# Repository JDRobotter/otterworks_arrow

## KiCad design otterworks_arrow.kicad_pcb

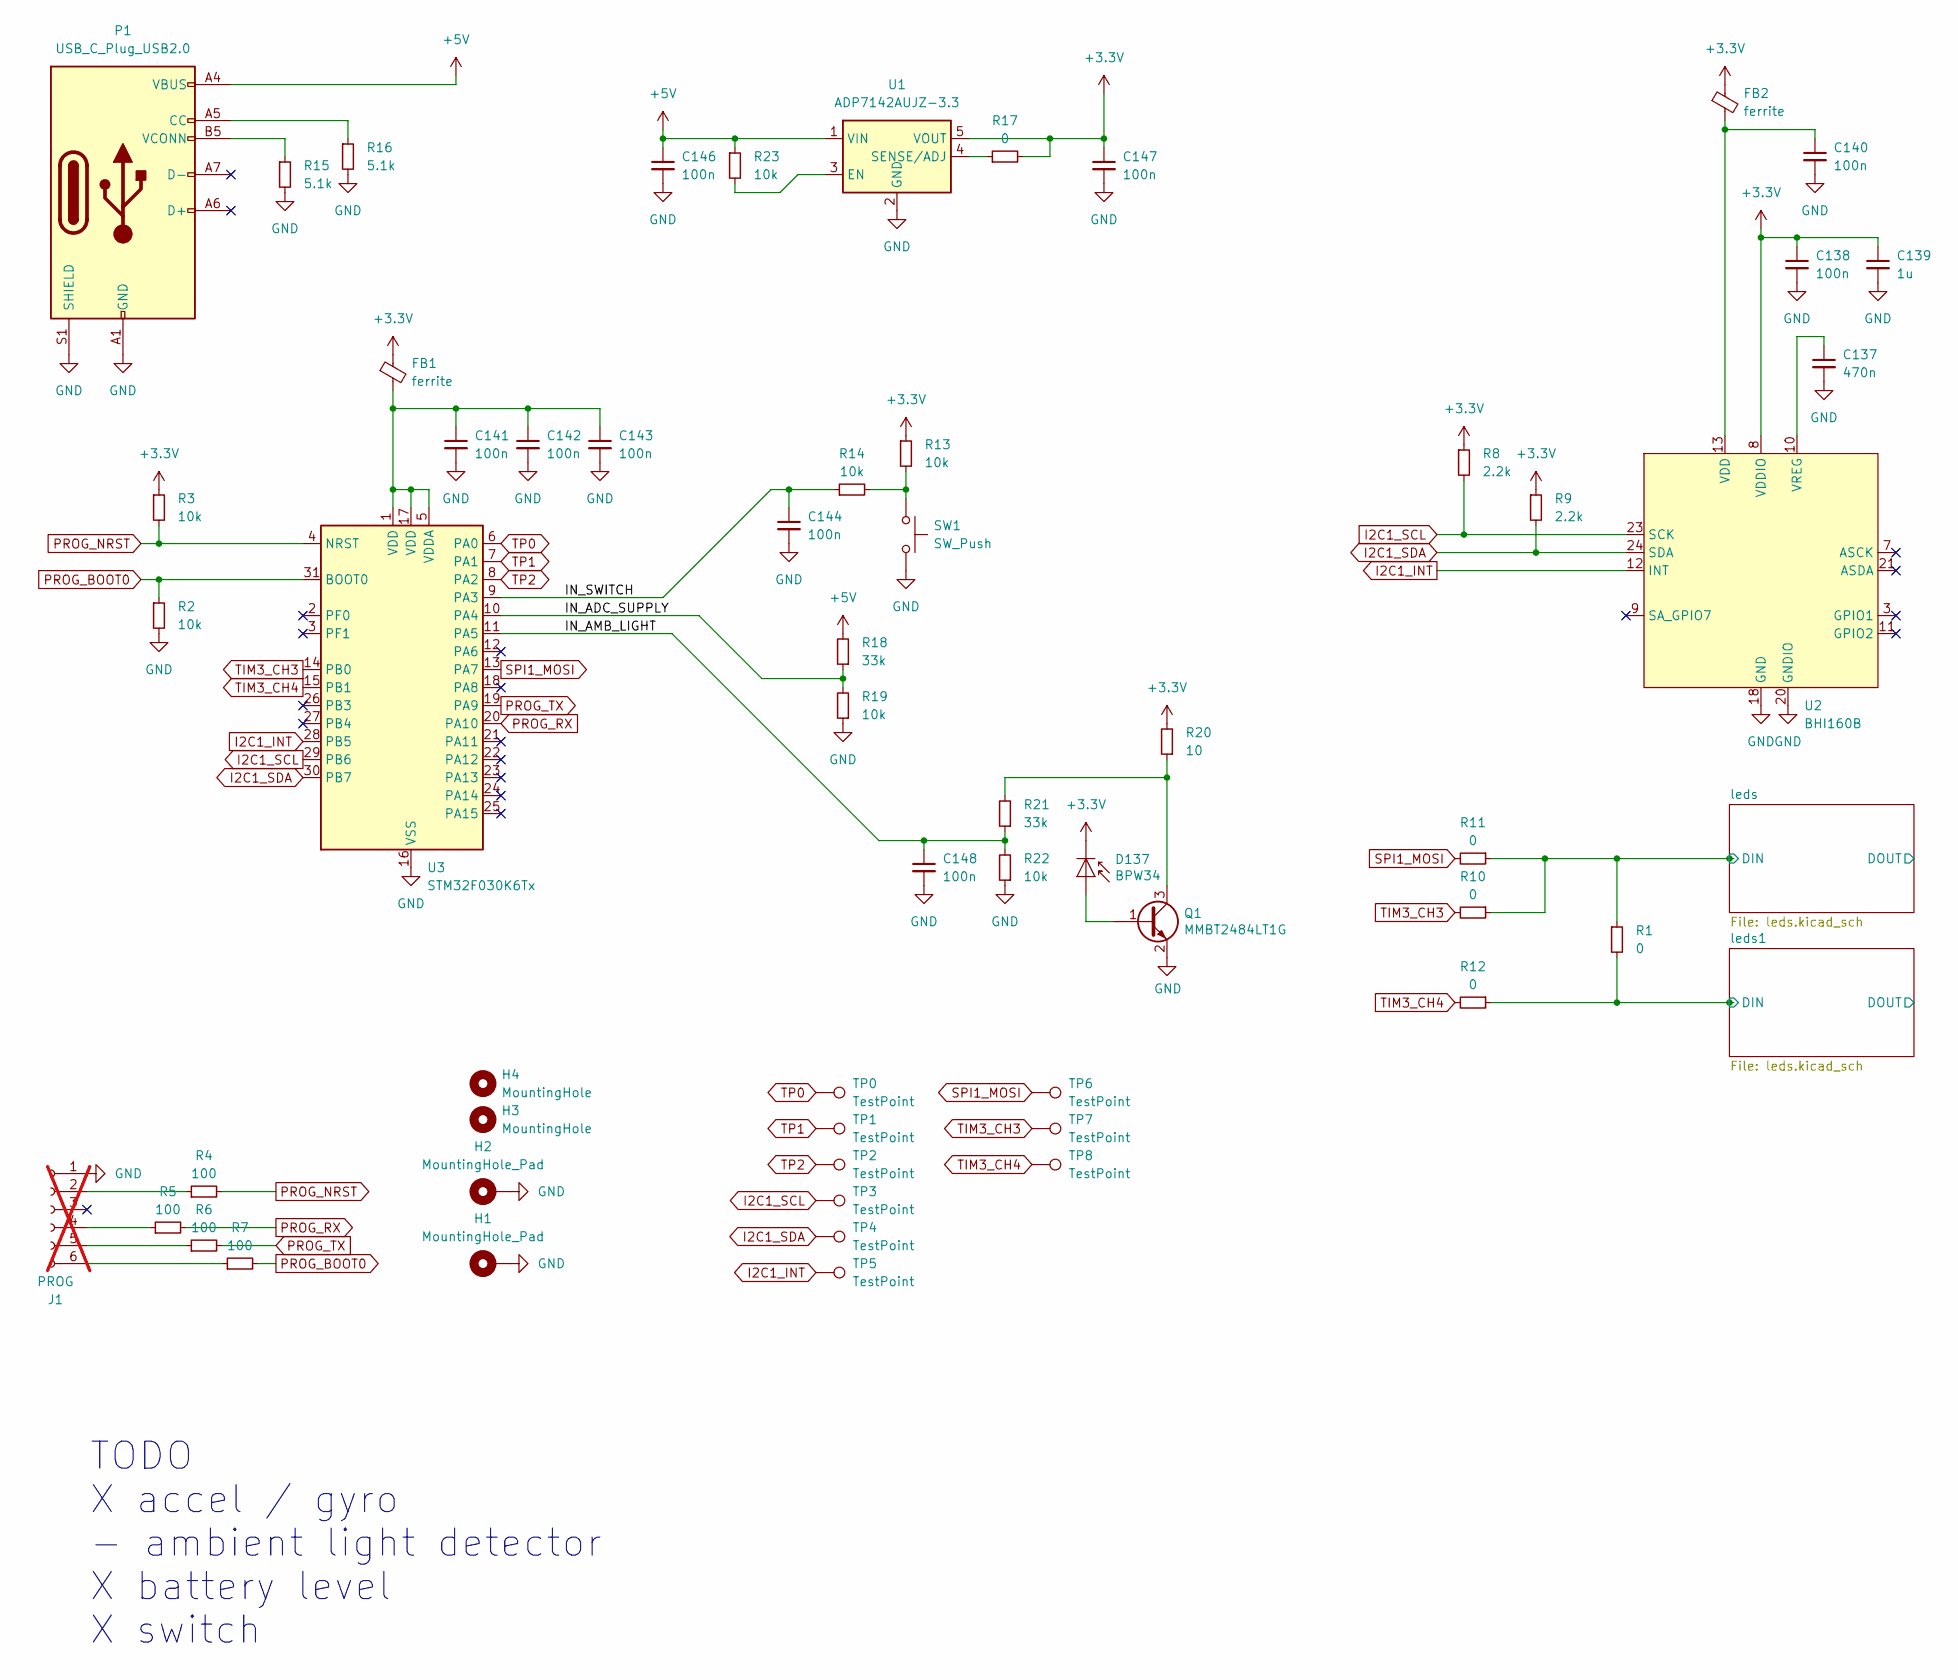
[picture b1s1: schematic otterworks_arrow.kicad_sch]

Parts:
C137: 470n; C_0603_1608Metric
C138, C140, C141, C142, C143, C144, C146, C147, C148: 100n; C_0603_1608Metric
C139: 1u; C_0603_1608Metric
D137: BPW34; Osram_DIL2_4.3x4.65mm_P5.08mm
FB1, FB2: ferrite; L_0603_1608Metric
H1, H2: MountingHole_Pad; MountingHole_3.2mm_M3_Pad
H3, H4: MountingHole; MountingHole_6mm
J1: PROG; PinHeader_1x06_P2.54mm_Vertical; not fitted
P1: USB_C_Plug_USB2.0; USB_C_Receptacle_HRO_TYPE-C-31-M-12
Q1: MMBT2484LT1G; SOT-23
R1, R10, R11, R12, R17: 0; R_0603_1608Metric
R2, R3, R13, R14, R19, R22, R23: 10k; R_0603_1608Metric
R4, R5, R6, R7: 100; R_0603_1608Metric
R8, R9: 2.2k; R_0603_1608Metric
R15, R16: 5.1k; R_0603_1608Metric
R18, R21: 33k; R_0603_1608Metric
R20: 10; R_0603_1608Metric
SW1: SW_Push; SW_Push_1P1T_NO_CK_KSC7xxJ
TP0, TP1, TP2, TP3, TP4, TP5, TP6, TP7, TP8: TestPoint; TestPoint_Pad_D1.0mm
U1: ADP7142AUJZ-3.3; TSOT-23-5
U2: BHI160B; LGA-24_3x3mm
U3: STM32F030K6Tx; LQFP-32_7x7mm_P0.8mm

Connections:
+3.3V: C138.1, C139.1, C147.1, D137.1 (K), FB1.1, FB2.1, R3.1, R8.1, R9.1, R13.1, R17.2, R20.2, U1.5 (VOUT), U2.8 (VDDIO)
+5V: C146.1, P1.A4 (VBUS), P1.A9 (VBUS), P1.B4 (VBUS), P1.B9 (VBUS), R18.2, R23.1, U1.1 (VIN); also elsewhere on the board
/IN_ADC_SUPPLY: R18.1, R19.2, U3.10 (PA4)
/IN_AMB_LIGHT: C148.1, R21.1, R22.2, U3.11 (PA5)
/IN_SWITCH: C144.1, R14.1, U3.9 (PA3)
/leds1/DIN: R1.2, R12.1; also elsewhere on the board
/leds/DIN: R1.1, R10.1, R11.1; also elsewhere on the board
GND: C137.2, C138.2, C139.2, C140.2, C141.2, C142.2, C143.2, C144.2, C146.2, C147.2, C148.2, H1.1, H2.1, J1.1, P1.A1 (GND), P1.A12 (GND), P1.B1 (GND), P1.B12 (GND), P1.S1 (SHIELD), Q1.2 (E), R2.2, R15.2, R16.2, R19.1, R22.1, SW1.2, U1.2 (GND), U2.18 (GND), U2.20 (GNDIO), U3.16 (VSS), U3.32 (VSS); also elsewhere on the board
I2C1_INT: TP5.1, U2.12 (INT), U3.28 (PB5)
I2C1_SCL: R8.2, TP3.1, U2.23 (SCK), U3.29 (PB6)
I2C1_SDA: R9.2, TP4.1, U2.24 (SDA), U3.30 (PB7)
unnamed: D137.2 (A), Q1.1 (B)
unnamed: J1.2, R4.1
unnamed: J1.4, R5.1
unnamed: J1.5, R6.1
unnamed: J1.6, R7.1
unnamed: P1.A5 (CC), R16.1
unnamed: P1.B5 (VCONN), R15.1
unnamed: Q1.3 (C), R20.1, R21.2
unnamed: R13.2, R14.2, SW1.1
unnamed: R23.2, U1.3 (EN)
unnamed: R17.1, U1.4 (SENSE/ADJ)
unnamed: C140.1, FB2.2, U2.13 (VDD)
unnamed: C137.1, U2.10 (VREG)
unnamed: C141.1, C142.1, C143.1, FB1.2, U3.1 (VDD), U3.5 (VDDA), U3.17 (VDD)
PROG_BOOT0: R2.1, R7.2, U3.31 (BOOT0)
PROG_NRST: R3.2, R4.2, U3.4 (NRST)
PROG_RX: R5.2, U3.20 (PA10)
PROG_TX: R6.2, U3.19 (PA9)
SPI1_MOSI: R11.2, TP6.1, U3.13 (PA7)
TIM3_CH3: R10.2, TP7.1, U3.14 (PB0)
TIM3_CH4: R12.2, TP8.1, U3.15 (PB1)
TP0: TP0.1, U3.6 (PA0)
TP1: TP1.1, U3.7 (PA1)
TP2: TP2.1, U3.8 (PA2)

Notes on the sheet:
TODO X accel / gyro - ambient light detector X battery level X switch

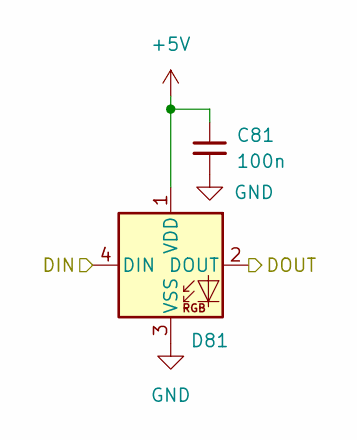
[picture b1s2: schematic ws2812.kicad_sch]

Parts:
C81: 100n; C_0603_1608Metric
D81: WS2812B-2020; LED_WS2812B_PLCC4_5.0x5.0mm_P3.2mm

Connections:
+5V: C81.1, D81.1 (VDD); also elsewhere on the board
/leds1/ws2812_59/DOUT: D81.4 (DIN); also elsewhere on the board
/leds1/ws2812_60/DOUT: D81.2 (DOUT); also elsewhere on the board
GND: C81.2, D81.3 (VSS); also elsewhere on the board

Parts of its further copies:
C1, C2, C3, C4, C5, C6, C7, C8, C9, C10, C11, C12, C13, C14, C15, C16, C17, C18, C19, C20, C21, C22, C23, C24, C25, C26, C27, C28, C29, C30, C31, C32, C33, C34, C35, C36, C37, C38, C39, C40, C41, C42, C43, C44, C45, C46, C47, C48, C49, C50, C51, C52, C53, C54, C55, C56, C57, C58, C59, C60, C61, C62, C63, C64, C65, C66, C67, C68, C69, C70, C71, C72, C73, C74, C75, C76, C77, C78, C79, C80, C82, C83, C84, C85, C86, C87, C88, C89, C90, C91, C92, C93, C94, C95, C96, C97, C98, C99, C100, C101, C102, C103, C104, C105, C106, C107, C108, C109, C110, C111, C112, C113, C114, C115, C116, C117, C118, C119, C120, C121, C122, C123, C124, C125, C126, C127, C128, C129, C130, C131, C132, C133, C134, C135, C136: 100n; C_0603_1608Metric
D1, D2, D3, D4, D5, D6, D7, D8, D9, D10, D11, D12, D13, D14, D15, D16, D17, D18, D19, D20, D21, D22, D23, D24, D25, D26, D27, D28, D29, D30, D31, D32, D33, D34, D35, D36, D37, D38, D39, D40, D41, D42, D43, D44, D45, D46, D47, D48, D49, D50, D51, D52, D53, D54, D55, D56, D57, D58, D59, D60, D61, D62, D63, D64, D65, D66, D67, D68, D69, D70, D71, D72, D73, D74, D75, D76, D77, D78, D79, D80, D82, D83, D84, D85, D86, D87, D88, D89, D90, D91, D92, D93, D94, D95, D96, D97, D98, D99, D100, D101, D102, D103, D104, D105, D106, D107, D108, D109, D110, D111, D112, D113, D114, D115, D116, D117, D118, D119, D120, D121, D122, D123, D124, D125, D126, D127, D128, D129, D130, D131, D132, D133, D134, D135, D136: WS2812B-2020; LED_WS2812B_PLCC4_5.0x5.0mm_P3.2mm

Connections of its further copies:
+5V: C1.1, C2.1, C3.1, C4.1, C5.1, C6.1, C7.1, C8.1, C9.1, C10.1, C11.1, C12.1, C13.1, C14.1, C15.1, C16.1, C17.1, C18.1, C19.1, C20.1, C21.1, C22.1, C23.1, C24.1, C25.1, C26.1, C27.1, C28.1, C29.1, C30.1, C31.1, C32.1, C33.1, C34.1, C35.1, C36.1, C37.1, C38.1, C39.1, C40.1, C41.1, C42.1, C43.1, C44.1, C45.1, C46.1, C47.1, C48.1, C49.1, C50.1, C51.1, C52.1, C53.1, C54.1, C55.1, C56.1, C57.1, C58.1, C59.1, C60.1, C61.1, C62.1, C63.1, C64.1, C65.1, C66.1, C67.1, C68.1, C69.1, C70.1, C71.1, C72.1, C73.1, C74.1, C75.1, C76.1, C77.1, C78.1, C79.1, C80.1, C82.1, C83.1, C84.1, C85.1, C86.1, C87.1, C88.1, C89.1, C90.1, C91.1, C92.1, C93.1, C94.1, C95.1, C96.1, C97.1, C98.1, C99.1, C100.1, C101.1, C102.1, C103.1, C104.1, C105.1, C106.1, C107.1, C108.1, C109.1, C110.1, C111.1, C112.1, C113.1, C114.1, C115.1, C116.1, C117.1, C118.1, C119.1, C120.1, C121.1, C122.1, C123.1, C124.1, C125.1, C126.1, C127.1, C128.1, C129.1, C130.1, C131.1, C132.1, C133.1, C134.1, C135.1, C136.1, D1.1 (VDD), D2.1 (VDD), D3.1 (VDD), D4.1 (VDD), D5.1 (VDD), D6.1 (VDD), D7.1 (VDD), D8.1 (VDD), D9.1 (VDD), D10.1 (VDD), D11.1 (VDD), D12.1 (VDD), D13.1 (VDD), D14.1 (VDD), D15.1 (VDD), D16.1 (VDD), D17.1 (VDD), D18.1 (VDD), D19.1 (VDD), D20.1 (VDD), D21.1 (VDD), D22.1 (VDD), D23.1 (VDD), D24.1 (VDD), D25.1 (VDD), D26.1 (VDD), D27.1 (VDD), D28.1 (VDD), D29.1 (VDD), D30.1 (VDD), D31.1 (VDD), D32.1 (VDD), D33.1 (VDD), D34.1 (VDD), D35.1 (VDD), D36.1 (VDD), D37.1 (VDD), D38.1 (VDD), D39.1 (VDD), D40.1 (VDD), D41.1 (VDD), D42.1 (VDD), D43.1 (VDD), D44.1 (VDD), D45.1 (VDD), D46.1 (VDD), D47.1 (VDD), D48.1 (VDD), D49.1 (VDD), D50.1 (VDD), D51.1 (VDD), D52.1 (VDD), D53.1 (VDD), D54.1 (VDD), D55.1 (VDD), D56.1 (VDD), D57.1 (VDD), D58.1 (VDD), D59.1 (VDD), D60.1 (VDD), D61.1 (VDD), D62.1 (VDD), D63.1 (VDD), D64.1 (VDD), D65.1 (VDD), D66.1 (VDD), D67.1 (VDD), D68.1 (VDD), D69.1 (VDD), D70.1 (VDD), D71.1 (VDD), D72.1 (VDD), D73.1 (VDD), D74.1 (VDD), D75.1 (VDD), D76.1 (VDD), D77.1 (VDD), D78.1 (VDD), D79.1 (VDD), D80.1 (VDD), D82.1 (VDD), D83.1 (VDD), D84.1 (VDD), D85.1 (VDD), D86.1 (VDD), D87.1 (VDD), D88.1 (VDD), D89.1 (VDD), D90.1 (VDD), D91.1 (VDD), D92.1 (VDD), D93.1 (VDD), D94.1 (VDD), D95.1 (VDD), D96.1 (VDD), D97.1 (VDD), D98.1 (VDD), D99.1 (VDD), D100.1 (VDD), D101.1 (VDD), D102.1 (VDD), D103.1 (VDD), D104.1 (VDD), D105.1 (VDD), D106.1 (VDD), D107.1 (VDD), D108.1 (VDD), D109.1 (VDD), D110.1 (VDD), D111.1 (VDD), D112.1 (VDD), D113.1 (VDD), D114.1 (VDD), D115.1 (VDD), D116.1 (VDD), D117.1 (VDD), D118.1 (VDD), D119.1 (VDD), D120.1 (VDD), D121.1 (VDD), D122.1 (VDD), D123.1 (VDD), D124.1 (VDD), D125.1 (VDD), D126.1 (VDD), D127.1 (VDD), D128.1 (VDD), D129.1 (VDD), D130.1 (VDD), D131.1 (VDD), D132.1 (VDD), D133.1 (VDD), D134.1 (VDD), D135.1 (VDD), D136.1 (VDD); also elsewhere on the board
/leds1/DIN: D103.4 (DIN); also elsewhere on the board
/leds1/DOUT: D133.2 (DOUT)
/leds1/ws2812_1/DOUT: D103.2 (DOUT), D105.4 (DIN)
/leds1/ws2812_2/DOUT: D102.4 (DIN), D105.2 (DOUT)
/leds1/ws2812_3/DOUT: D99.4 (DIN), D102.2 (DOUT)
/leds1/ws2812_4/DOUT: D99.2 (DOUT), D100.4 (DIN)
/leds1/ws2812_5/DOUT: D100.2 (DOUT), D101.4 (DIN)
/leds1/ws2812_6/DOUT: D88.4 (DIN), D101.2 (DOUT)
/leds1/ws2812_7/DOUT: D88.2 (DOUT), D89.4 (DIN)
/leds1/ws2812_8/DOUT: D89.2 (DOUT), D90.4 (DIN)
/leds1/ws2812_10/DIN: D90.2 (DOUT), D91.4 (DIN)
/leds1/ws2812_10/DOUT: D91.2 (DOUT), D112.4 (DIN)
/leds1/ws2812_11/DOUT: D111.4 (DIN), D112.2 (DOUT)
/leds1/ws2812_12/DOUT: D108.4 (DIN), D111.2 (DOUT)
/leds1/ws2812_13/DOUT: D108.2 (DOUT), D124.4 (DIN)
/leds1/ws2812_14/DOUT: D122.4 (DIN), D124.2 (DOUT)
/leds1/ws2812_15/DOUT: D122.2 (DOUT), D125.4 (DIN)
/leds1/ws2812_16/DOUT: D125.2 (DOUT), D126.4 (DIN)
/leds1/ws2812_17/DOUT: D123.4 (DIN), D126.2 (DOUT)
/leds1/ws2812_18/DOUT: D69.4 (DIN), D123.2 (DOUT)
/leds1/ws2812_19/DOUT: D69.2 (DOUT), D104.4 (DIN)
/leds1/ws2812_20/DOUT: D78.4 (DIN), D104.2 (DOUT)
/leds1/ws2812_21/DOUT: D76.4 (DIN), D78.2 (DOUT)
/leds1/ws2812_22/DOUT: D76.2 (DOUT), D79.4 (DIN)
/leds1/ws2812_23/DOUT: D79.2 (DOUT), D80.4 (DIN)
/leds1/ws2812_24/DOUT: D77.4 (DIN), D80.2 (DOUT)
/leds1/ws2812_25/DOUT: D77.2 (DOUT), D93.4 (DIN)
/leds1/ws2812_26/DOUT: D92.4 (DIN), D93.2 (DOUT)
/leds1/ws2812_27/DOUT: D92.2 (DOUT), D117.4 (DIN)
/leds1/ws2812_28/DOUT: D117.2 (DOUT), D121.4 (DIN)
/leds1/ws2812_29/DOUT: D118.4 (DIN), D121.2 (DOUT)
/leds1/ws2812_30/DOUT: D109.4 (DIN), D118.2 (DOUT)
/leds1/ws2812_31/DOUT: D107.4 (DIN), D109.2 (DOUT)
/leds1/ws2812_32/DOUT: D107.2 (DOUT), D130.4 (DIN)
/leds1/ws2812_33/DOUT: D129.4 (DIN), D130.2 (DOUT)
/leds1/ws2812_34/DOUT: D128.4 (DIN), D129.2 (DOUT)
/leds1/ws2812_35/DOUT: D127.4 (DIN), D128.2 (DOUT)
/leds1/ws2812_36/DOUT: D75.4 (DIN), D127.2 (DOUT)
/leds1/ws2812_37/DOUT: D73.4 (DIN), D75.2 (DOUT)
/leds1/ws2812_38/DOUT: D70.4 (DIN), D73.2 (DOUT)
/leds1/ws2812_39/DOUT: D70.2 (DOUT), D98.4 (DIN)
/leds1/ws2812_40/DOUT: D94.4 (DIN), D98.2 (DOUT)
/leds1/ws2812_41/DOUT: D94.2 (DOUT), D96.4 (DIN)
/leds1/ws2812_42/DOUT: D87.4 (DIN), D96.2 (DOUT)
/leds1/ws2812_43/DOUT: D87.2 (DOUT), D116.4 (DIN)
/leds1/ws2812_44/DOUT: D116.2 (DOUT), D119.4 (DIN)
/leds1/ws2812_45/DOUT: D85.4 (DIN), D119.2 (DOUT)
/leds1/ws2812_46/DOUT: D85.2 (DOUT), D120.4 (DIN)
/leds1/ws2812_47/DOUT: D120.2 (DOUT), D134.4 (DIN)
/leds1/ws2812_48/DOUT: D106.4 (DIN), D134.2 (DOUT)
/leds1/ws2812_49/DOUT: D106.2 (DOUT), D110.4 (DIN)
/leds1/ws2812_50/DOUT: D110.2 (DOUT), D132.4 (DIN)
/leds1/ws2812_51/DOUT: D113.4 (DIN), D132.2 (DOUT)
/leds1/ws2812_52/DOUT: D113.2 (DOUT), D115.4 (DIN)
/leds1/ws2812_53/DOUT: D114.4 (DIN), D115.2 (DOUT)
/leds1/ws2812_54/DOUT: D74.4 (DIN), D114.2 (DOUT)
/leds1/ws2812_55/DOUT: D72.4 (DIN), D74.2 (DOUT)
/leds1/ws2812_56/DOUT: D71.4 (DIN), D72.2 (DOUT)
/leds1/ws2812_57/DOUT: D71.2 (DOUT), D95.4 (DIN)
/leds1/ws2812_58/DOUT: D95.2 (DOUT), D97.4 (DIN)
/leds1/ws2812_59/DOUT: D97.2 (DOUT); also elsewhere on the board
/leds1/ws2812_60/DOUT: D84.4 (DIN); also elsewhere on the board
/leds1/ws2812_61/DOUT: D82.4 (DIN), D84.2 (DOUT)
/leds1/ws2812_62/DOUT: D82.2 (DOUT), D83.4 (DIN)
/leds1/ws2812_63/DOUT: D83.2 (DOUT), D86.4 (DIN)
/leds1/ws2812_64/DOUT: D86.2 (DOUT), D136.4 (DIN)
/leds1/ws2812_65/DOUT: D131.4 (DIN), D136.2 (DOUT)
/leds1/ws2812_66/DOUT: D131.2 (DOUT), D135.4 (DIN)
/leds1/ws2812_67/DOUT: D133.4 (DIN), D135.2 (DOUT)
/leds/DIN: D1.4 (DIN); also elsewhere on the board
/leds/DOUT: D68.2 (DOUT)
/leds/ws2812_1/DOUT: D1.2 (DOUT), D2.4 (DIN)
/leds/ws2812_2/DOUT: D2.2 (DOUT), D3.4 (DIN)
/leds/ws2812_3/DOUT: D3.2 (DOUT), D4.4 (DIN)
/leds/ws2812_4/DOUT: D4.2 (DOUT), D5.4 (DIN)
/leds/ws2812_5/DOUT: D5.2 (DOUT), D6.4 (DIN)
/leds/ws2812_6/DOUT: D6.2 (DOUT), D7.4 (DIN)
/leds/ws2812_7/DOUT: D7.2 (DOUT), D8.4 (DIN)
/leds/ws2812_8/DOUT: D8.2 (DOUT), D9.4 (DIN)
/leds/ws2812_10/DIN: D9.2 (DOUT), D10.4 (DIN)
/leds/ws2812_10/DOUT: D10.2 (DOUT), D11.4 (DIN)
/leds/ws2812_11/DOUT: D11.2 (DOUT), D12.4 (DIN)
/leds/ws2812_12/DOUT: D12.2 (DOUT), D13.4 (DIN)
/leds/ws2812_13/DOUT: D13.2 (DOUT), D14.4 (DIN)
/leds/ws2812_14/DOUT: D14.2 (DOUT), D15.4 (DIN)
/leds/ws2812_15/DOUT: D15.2 (DOUT), D16.4 (DIN)
/leds/ws2812_16/DOUT: D16.2 (DOUT), D17.4 (DIN)
/leds/ws2812_17/DOUT: D17.2 (DOUT), D18.4 (DIN)
/leds/ws2812_18/DOUT: D18.2 (DOUT), D19.4 (DIN)
/leds/ws2812_19/DOUT: D19.2 (DOUT), D20.4 (DIN)
/leds/ws2812_20/DOUT: D20.2 (DOUT), D21.4 (DIN)
/leds/ws2812_21/DOUT: D21.2 (DOUT), D22.4 (DIN)
/leds/ws2812_22/DOUT: D22.2 (DOUT), D23.4 (DIN)
/leds/ws2812_23/DOUT: D23.2 (DOUT), D24.4 (DIN)
/leds/ws2812_24/DOUT: D24.2 (DOUT), D25.4 (DIN)
/leds/ws2812_25/DOUT: D25.2 (DOUT), D26.4 (DIN)
/leds/ws2812_26/DOUT: D26.2 (DOUT), D27.4 (DIN)
/leds/ws2812_27/DOUT: D27.2 (DOUT), D28.4 (DIN)
/leds/ws2812_28/DOUT: D28.2 (DOUT), D29.4 (DIN)
/leds/ws2812_29/DOUT: D29.2 (DOUT), D30.4 (DIN)
/leds/ws2812_30/DOUT: D30.2 (DOUT), D31.4 (DIN)
/leds/ws2812_31/DOUT: D31.2 (DOUT), D32.4 (DIN)
/leds/ws2812_32/DOUT: D32.2 (DOUT), D33.4 (DIN)
/leds/ws2812_33/DOUT: D33.2 (DOUT), D34.4 (DIN)
/leds/ws2812_34/DOUT: D34.2 (DOUT), D35.4 (DIN)
/leds/ws2812_35/DOUT: D35.2 (DOUT), D36.4 (DIN)
/leds/ws2812_36/DOUT: D36.2 (DOUT), D37.4 (DIN)
/leds/ws2812_37/DOUT: D37.2 (DOUT), D38.4 (DIN)
/leds/ws2812_38/DOUT: D38.2 (DOUT), D39.4 (DIN)
/leds/ws2812_39/DOUT: D39.2 (DOUT), D40.4 (DIN)
/leds/ws2812_40/DOUT: D40.2 (DOUT), D41.4 (DIN)
/leds/ws2812_41/DOUT: D41.2 (DOUT), D42.4 (DIN)
/leds/ws2812_42/DOUT: D42.2 (DOUT), D43.4 (DIN)
/leds/ws2812_43/DOUT: D43.2 (DOUT), D44.4 (DIN)
/leds/ws2812_44/DOUT: D44.2 (DOUT), D45.4 (DIN)
/leds/ws2812_45/DOUT: D45.2 (DOUT), D46.4 (DIN)
/leds/ws2812_46/DOUT: D46.2 (DOUT), D47.4 (DIN)
/leds/ws2812_47/DOUT: D47.2 (DOUT), D48.4 (DIN)
/leds/ws2812_48/DOUT: D48.2 (DOUT), D49.4 (DIN)
/leds/ws2812_49/DOUT: D49.2 (DOUT), D50.4 (DIN)
/leds/ws2812_50/DOUT: D50.2 (DOUT), D51.4 (DIN)
/leds/ws2812_51/DOUT: D51.2 (DOUT), D52.4 (DIN)
/leds/ws2812_52/DOUT: D52.2 (DOUT), D53.4 (DIN)
/leds/ws2812_53/DOUT: D53.2 (DOUT), D54.4 (DIN)
/leds/ws2812_54/DOUT: D54.2 (DOUT), D55.4 (DIN)
/leds/ws2812_55/DOUT: D55.2 (DOUT), D56.4 (DIN)
/leds/ws2812_56/DOUT: D56.2 (DOUT), D57.4 (DIN)
/leds/ws2812_57/DOUT: D57.2 (DOUT), D58.4 (DIN)
/leds/ws2812_58/DOUT: D58.2 (DOUT), D59.4 (DIN)
/leds/ws2812_59/DOUT: D59.2 (DOUT), D60.4 (DIN)
/leds/ws2812_60/DOUT: D60.2 (DOUT), D61.4 (DIN)
/leds/ws2812_61/DOUT: D61.2 (DOUT), D62.4 (DIN)
/leds/ws2812_62/DOUT: D62.2 (DOUT), D63.4 (DIN)
/leds/ws2812_63/DOUT: D63.2 (DOUT), D64.4 (DIN)
/leds/ws2812_64/DOUT: D64.2 (DOUT), D65.4 (DIN)
/leds/ws2812_65/DOUT: D65.2 (DOUT), D66.4 (DIN)
/leds/ws2812_66/DOUT: D66.2 (DOUT), D67.4 (DIN)
/leds/ws2812_67/DOUT: D67.2 (DOUT), D68.4 (DIN)
GND: C1.2, C2.2, C3.2, C4.2, C5.2, C6.2, C7.2, C8.2, C9.2, C10.2, C11.2, C12.2, C13.2, C14.2, C15.2, C16.2, C17.2, C18.2, C19.2, C20.2, C21.2, C22.2, C23.2, C24.2, C25.2, C26.2, C27.2, C28.2, C29.2, C30.2, C31.2, C32.2, C33.2, C34.2, C35.2, C36.2, C37.2, C38.2, C39.2, C40.2, C41.2, C42.2, C43.2, C44.2, C45.2, C46.2, C47.2, C48.2, C49.2, C50.2, C51.2, C52.2, C53.2, C54.2, C55.2, C56.2, C57.2, C58.2, C59.2, C60.2, C61.2, C62.2, C63.2, C64.2, C65.2, C66.2, C67.2, C68.2, C69.2, C70.2, C71.2, C72.2, C73.2, C74.2, C75.2, C76.2, C77.2, C78.2, C79.2, C80.2, C82.2, C83.2, C84.2, C85.2, C86.2, C87.2, C88.2, C89.2, C90.2, C91.2, C92.2, C93.2, C94.2, C95.2, C96.2, C97.2, C98.2, C99.2, C100.2, C101.2, C102.2, C103.2, C104.2, C105.2, C106.2, C107.2, C108.2, C109.2, C110.2, C111.2, C112.2, C113.2, C114.2, C115.2, C116.2, C117.2, C118.2, C119.2, C120.2, C121.2, C122.2, C123.2, C124.2, C125.2, C126.2, C127.2, C128.2, C129.2, C130.2, C131.2, C132.2, C133.2, C134.2, C135.2, C136.2, D1.3 (VSS), D2.3 (VSS), D3.3 (VSS), D4.3 (VSS), D5.3 (VSS), D6.3 (VSS), D7.3 (VSS), D8.3 (VSS), D9.3 (VSS), D10.3 (VSS), D11.3 (VSS), D12.3 (VSS), D13.3 (VSS), D14.3 (VSS), D15.3 (VSS), D16.3 (VSS), D17.3 (VSS), D18.3 (VSS), D19.3 (VSS), D20.3 (VSS), D21.3 (VSS), D22.3 (VSS), D23.3 (VSS), D24.3 (VSS), D25.3 (VSS), D26.3 (VSS), D27.3 (VSS), D28.3 (VSS), D29.3 (VSS), D30.3 (VSS), D31.3 (VSS), D32.3 (VSS), D33.3 (VSS), D34.3 (VSS), D35.3 (VSS), D36.3 (VSS), D37.3 (VSS), D38.3 (VSS), D39.3 (VSS), D40.3 (VSS), D41.3 (VSS), D42.3 (VSS), D43.3 (VSS), D44.3 (VSS), D45.3 (VSS), D46.3 (VSS), D47.3 (VSS), D48.3 (VSS), D49.3 (VSS), D50.3 (VSS), D51.3 (VSS), D52.3 (VSS), D53.3 (VSS), D54.3 (VSS), D55.3 (VSS), D56.3 (VSS), D57.3 (VSS), D58.3 (VSS), D59.3 (VSS), D60.3 (VSS), D61.3 (VSS), D62.3 (VSS), D63.3 (VSS), D64.3 (VSS), D65.3 (VSS), D66.3 (VSS), D67.3 (VSS), D68.3 (VSS), D69.3 (VSS), D70.3 (VSS), D71.3 (VSS), D72.3 (VSS), D73.3 (VSS), D74.3 (VSS), D75.3 (VSS), D76.3 (VSS), D77.3 (VSS), D78.3 (VSS), D79.3 (VSS), D80.3 (VSS), D82.3 (VSS), D83.3 (VSS), D84.3 (VSS), D85.3 (VSS), D86.3 (VSS), D87.3 (VSS), D88.3 (VSS), D89.3 (VSS), D90.3 (VSS), D91.3 (VSS), D92.3 (VSS), D93.3 (VSS), D94.3 (VSS), D95.3 (VSS), D96.3 (VSS), D97.3 (VSS), D98.3 (VSS), D99.3 (VSS), D100.3 (VSS), D101.3 (VSS), D102.3 (VSS), D103.3 (VSS), D104.3 (VSS), D105.3 (VSS), D106.3 (VSS), D107.3 (VSS), D108.3 (VSS), D109.3 (VSS), D110.3 (VSS), D111.3 (VSS), D112.3 (VSS), D113.3 (VSS), D114.3 (VSS), D115.3 (VSS), D116.3 (VSS), D117.3 (VSS), D118.3 (VSS), D119.3 (VSS), D120.3 (VSS), D121.3 (VSS), D122.3 (VSS), D123.3 (VSS), D124.3 (VSS), D125.3 (VSS), D126.3 (VSS), D127.3 (VSS), D128.3 (VSS), D129.3 (VSS), D130.3 (VSS), D131.3 (VSS), D132.3 (VSS), D133.3 (VSS), D134.3 (VSS), D135.3 (VSS), D136.3 (VSS); also elsewhere on the board

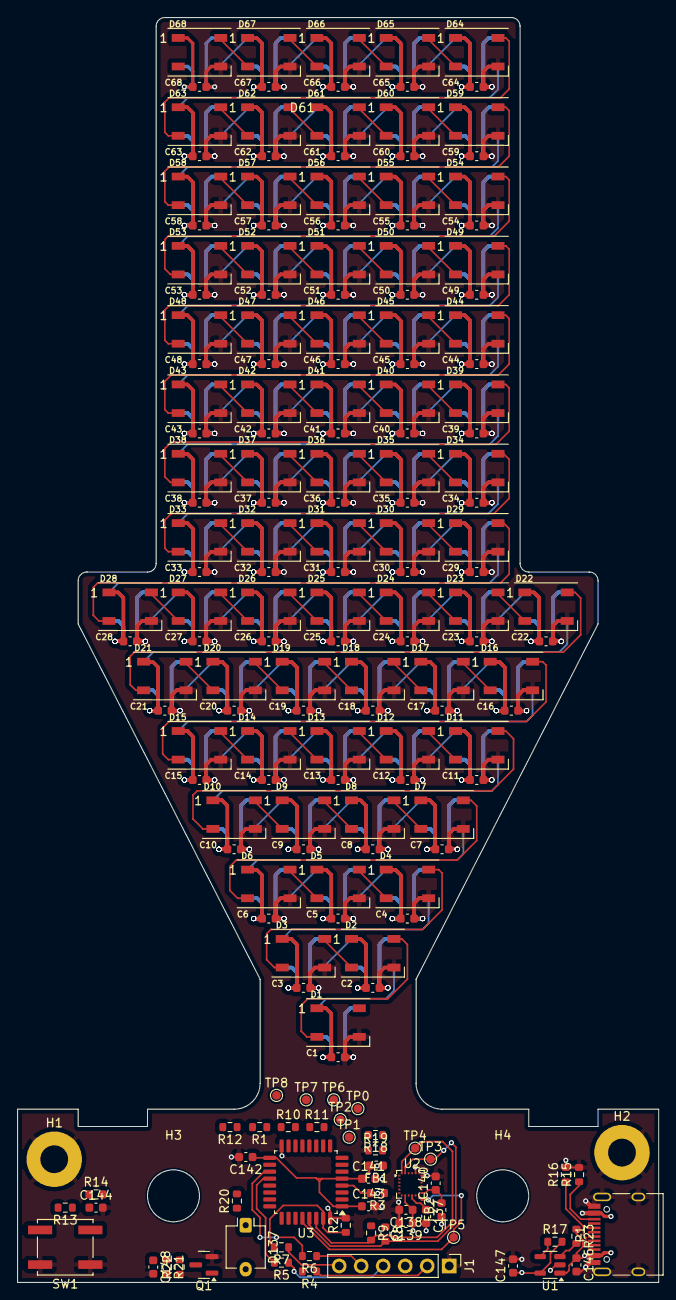
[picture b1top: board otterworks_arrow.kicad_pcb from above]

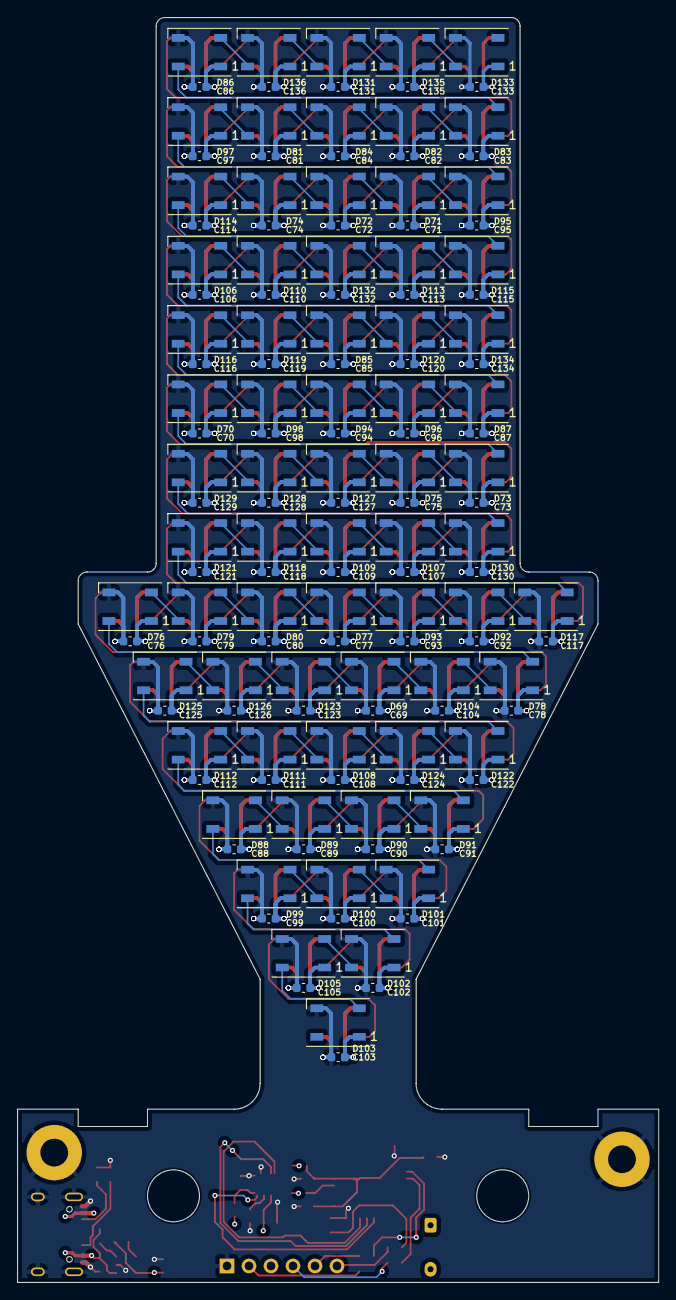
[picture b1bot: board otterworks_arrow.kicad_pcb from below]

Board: 4 copper layers, 74.0 x 146.0 mm, 329 parts (136 on the bottom side), 169 nets.

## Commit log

2024-08-18 top LED layer impl done
2024-08-19 bottom side done
2024-08-25 bosh IMU addded
